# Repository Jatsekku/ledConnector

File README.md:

# ledConnector

Small connector PCB designed for noname ZigBee controller (version RGBCW): [this one](https://pl.aliexpress.com/item/1005005634005243.html?srcSns=sns_Copy&spreadType=socialShare&bizType=ProductDetail&social_params=60811259683&aff_fcid=368de0fa499b440092f7d4af70d54110-1727819655069-06785-_Ext7h7F&tt=MG&fbclid=IwY2xjawFpTtZleHRuA2FlbQIxMAABHa1f0QjnrHqwywSU5HHgteS7Dx3SYLz70TDuLomQzgZcnZJDuDSwwBwSYA_aem_xyvfc5u3CarVrbAd5t3e8g&aff_fsk=_Ext7h7F&aff_platform=default&sk=_Ext7h7F&aff_trace_key=368de0fa499b440092f7d4af70d54110-1727819655069-06785-_Ext7h7F&shareId=60811259683&businessType=ProductDetail&platform=AE&terminal_id=61640e1edf5442f1ac2230fec42363f5&afSmartRedirect=y)

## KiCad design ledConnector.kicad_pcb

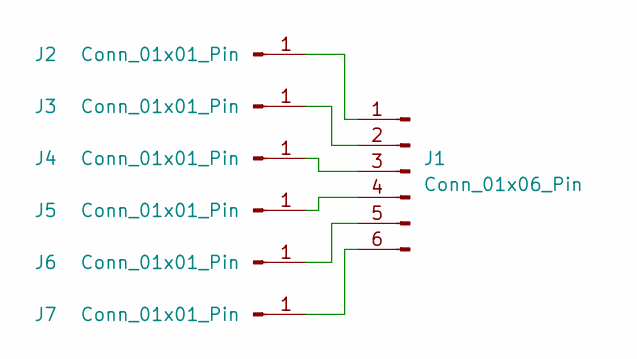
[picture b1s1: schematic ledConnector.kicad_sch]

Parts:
J1: Conn_01x06_Pin; PinHeader_1x06_P2.00mm_Vertical
J2, J3, J4, J5, J6, J7: Conn_01x01_Pin; Pin_D1.1mm_L8.5mm_W2.5mm_FlatFork

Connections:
unnamed: J1.1, J2.1
unnamed: J1.2, J3.1
unnamed: J1.3, J4.1
unnamed: J1.4, J5.1
unnamed: J1.5, J6.1
unnamed: J1.6, J7.1

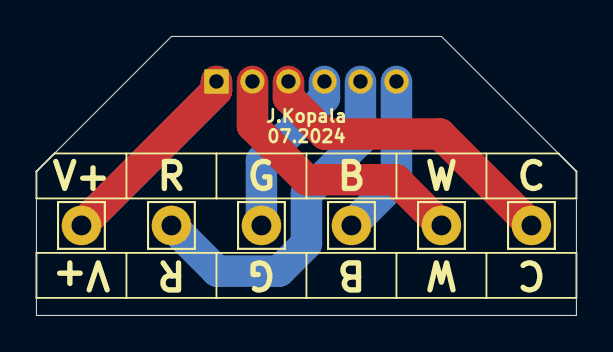
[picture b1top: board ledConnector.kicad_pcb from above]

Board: 2 copper layers, 30.0 x 15.5 mm, 7 parts (1 on the bottom side), 6 nets.

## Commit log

2024-10-01 feat: Add initial readme
2024-10-01 feat(sch): Add schematic
2024-10-01 feat(gerbers): Add gerbers output
2024-10-01 feat(git): Add .gitignore
2024-10-01 feat(PCB): Add PCB layout
2024-10-01 feat(README): Add 3D view
2024-10-01 feat(README): Add ZB controller reference
2024-11-11 fix(PCB): Change pin mapping
2024-11-11 fix(gerbers): Generate gerbers for fixed v2.0
